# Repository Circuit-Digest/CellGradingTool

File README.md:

# [CellGradingTool](https://circuitdigest.com/videos/diy-modular-cell-grading-machine)

<br>
Testing lithium-ion cells is critical for ensuring their performance, safety, and longevity, particularly in applications such as electric vehicles, energy storage systems, and portable electronics. As these cells can degrade over time, accurate grading tools are necessary to assess their charging, discharging, and overall capacity characteristics. This DIY modular cell grading tool addresses this need by providing a streamlined and scalable solution for testing multiple lithium-ion cells simultaneously while offering precise control over charging and discharging cycles. The tool’s modularity allows users to grade up to 250 cells in parallel, making it a versatile choice for both small and large-scale testing environments. At the heart of the tool is the STM32 G071KBU3 microcontroller, powered by an ADP7118 3.3V LDO regulator. The tool is designed to detect the voltage of each inserted cell and display it on a two-digit seven-segment display, providing instant feedback. When connected to the companion software, users can initiate a test, charging the cell at a constant current of 1A using the TP4056 IC. Upon reaching full charge, the system will disable the charging circuitry and transition into discharge mode, where the discharge current and voltage are monitored through the high-precision INA236 sensor. This setup ensures accurate tracking of both charging and discharging parameters, essential for detailed cell grading.
<br>
Communication between the tool and the PC is managed via the RS485 protocol, utilising the SP485REN transceiver IC. This allows us to connect multiple tools in parallel, with each module being independently controlled by the companion app. The discharge circuit uses an IRF540 MOSFET as a programable DC load and a current control circuit built around the MCP6486 op-amp, ensuring precise current regulation. The DAC output from the STM32G071 is used for adjusting the discharge current, allowing for highly accurate measurements of cell performance under load conditions. The companion software, written in Processing, provides a user-friendly interface for controlling up to 8 modules, with the flexibility to expand to 250 modules. Users can set parameters such as discharge current and voltage limits for each module independently and start tests with a single button click. The software also includes a feature for graphing the discharge voltage curve, providing valuable insights into the cell’s behaviour over time. Even if the cell is removed, the tool retains the test data, ensuring no loss of critical information. With this tool, users can efficiently grade lithium-ion cells and make informed decisions about their suitability for various applications.

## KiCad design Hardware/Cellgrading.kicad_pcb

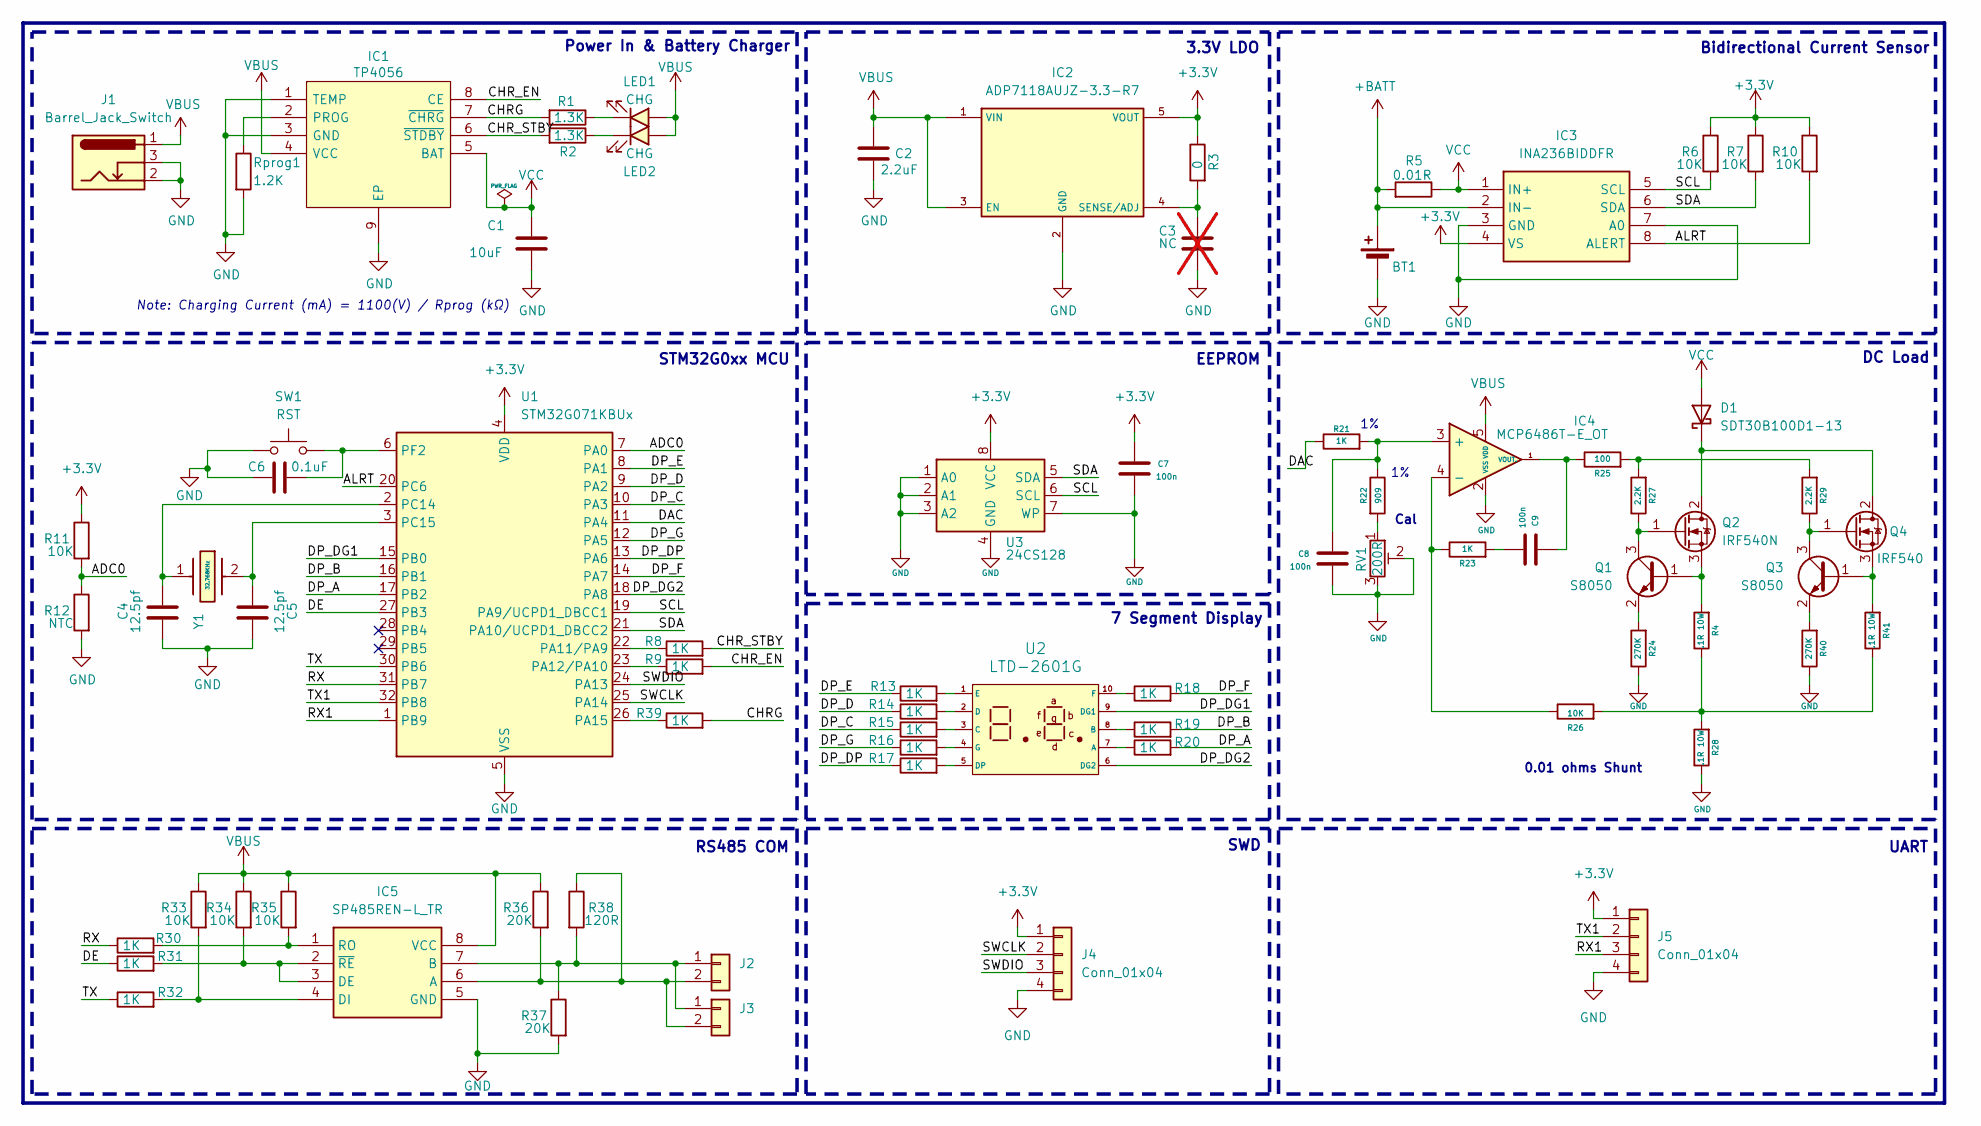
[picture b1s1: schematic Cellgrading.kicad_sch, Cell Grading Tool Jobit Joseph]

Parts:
BT1: Battery_Cell; BAT_1042
C1: 10uF; C_0603_1608Metric
C2: 2.2uF; C_0603_1608Metric
C3: NC; C_0603_1608Metric; not fitted
C4, C5: 12.5pf; C_0603_1608Metric
C6: 0.1uF; C_0603_1608Metric
C7, C8, C9: 100n; C_0603_1608Metric
D1: SDT30B100D1-13; TO252_DIO
IC1: TP4056; SOIC127P600X175-9N; Manufacturer_Part_Number TP4056-42-ESOP8
IC2: ADP7118AUJZ-3.3-R7; SOT95P280X100-5N; Mouser Part Number 584-ADP7118AUJZ3.3R7
IC3: INA236BIDDFR; SOT65P280X110-8N; Mouser Part Number 595-INA236BIDDFR
IC4: MCP6486T-E_OT; SOT95P280X145-5N; Mouser Part Number 494-MCP6486T-E/OT
IC5: SP485REN-L_TR; SOIC127P600X175-8N; Mouser Part Number 701-SP485REN-L/TR
J1: Barrel_Jack_Switch; BarrelJack_Kycon_KLDX-0202-xC_Horizontal
J2, J3: Conn_01x02; JST_PH_S2B-PH-SM4-TB_1x02-1MP_P2.00mm_Horizontal
J4, J5: Conn_01x04; PinHeader_1x04_P2.54mm_Vertical
LED1, LED2: CHG; LED_0603_1608Metric
Q1, Q3: S8050; SOT-23
Q2: IRF540N; TO-220-3_Vertical
Q4: IRF540; TO-220-3_Vertical
R1, R2: 1.3K; R_0603_1608Metric
R3: 0; R_0603_1608Metric
R4, R28, R41: .1R 10W; WSHP2818R0200FEA
R5: 0.01R; WSHP2818R0200FEA
R6, R7, R10, R11, R26, R33, R34, R35: 10K; R_0603_1608Metric
R8, R9, R13, R14, R15, R16, R17, R18, R19, R20, R21, R23, R30, R31, R32, R39: 1K; R_0603_1608Metric
R12: NTC; JST_PH_B2B-PH-K_1x02_P2.00mm_Vertical
R22: 909; R_0603_1608Metric
R24, R40: 270K; R_0603_1608Metric
R25: 100; R_0603_1608Metric
R27, R29: 2.2K; R_0603_1608Metric
R36, R37: 20K; R_0603_1608Metric
R38: 120R; R_0603_1608Metric
RV1: 200R; TRIM_3296W-1-104
Rprog1: 1.2K; R_0603_1608Metric
SW1: RST; Tactile 3x4x2mm TS-A010
U1: STM32G071KBUx; QFN-32-1EP_5x5mm_P0.5mm_EP3.45x3.45mm
U2: LTD-2601G; LTD-2601G_LTO
U3: 24CS128; SOIC-8_3.9x4.9mm_P1.27mm
Y1: 32.768KHz; ECS327734BCTR; Mouser Part Number 520-ECS-.327-7-34BCT

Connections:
+3.3V: C7.1, IC2.5 (VOUT), IC3.4 (VS), J4.1, J5.1, R3.1, R6.1, R7.1, R10.1, R11.1, U1.4 (VDD), U3.8 (VCC)
+BATT: BT1.1 (+), IC3.2 (IN-), R5.2
/ADC0: R11.2, R12.1, U1.7 (PA0)
/ALRT: IC3.8 (ALERT), R10.2, U1.20 (PC6)
/CHRG: IC1.7 (~CHRG), R1.2, R39.2
/CHR_EN: IC1.8 (CE), R9.2
/CHR_STBY: IC1.6 (~STDBY), R2.2, R8.2
/DAC: R21.1, U1.11 (PA4)
/DE: R31.1, U1.27 (PB3)
/DP_A: R20.2, U1.17 (PB2)
/DP_B: R19.2, U1.16 (PB1)
/DP_C: R15.1, U1.10 (PA3)
/DP_D: R14.1, U1.9 (PA2)
/DP_DG1: U1.15 (PB0), U2.9 (DG1)
/DP_DG2: U1.18 (PA8), U2.6 (DG2)
/DP_DP: R17.1, U1.13 (PA6)
/DP_E: R13.1, U1.8 (PA1)
/DP_F: R18.2, U1.14 (PA7)
/DP_G: R16.1, U1.12 (PA5)
/RX: R30.1, U1.31 (PB7)
/RX1: J5.3, U1.1 (PB9)
/SCL: IC3.5 (SCL), R6.2, U1.19 (PA9/UCPD1_DBCC1), U3.6 (SCL)
/SDA: IC3.6 (SDA), R7.2, U1.21 (PA10/UCPD1_DBCC2), U3.5 (SDA)
/SWCLK: J4.2, U1.25 (PA14)
/SWDIO: J4.3, U1.24 (PA13)
/TX: R32.1, U1.30 (PB6)
/TX1: J5.2, U1.32 (PB8)
GND: BT1.2 (-), C1.2, C2.2, C3.2, C4.2, C5.2, C6.1, C7.2, C8.2, IC1.1 (TEMP), IC1.3 (GND), IC1.9 (EP), IC2.2 (GND), IC3.3 (GND), IC3.7 (A0), IC4.2 (VSS), IC5.5 (GND), J1.2, J1.3, J4.4, J5.4, R12.2, R24.1, R28.1, R37.2, R40.1, RV1.2, RV1.3, Rprog1.2, SW1.1, U1.5 (VSS), U1.33 (VSS), U3.1 (A0), U3.2 (A1), U3.3 (A2), U3.4 (GND), U3.7 (WP)
unnamed: C9.2, R23.2
unnamed: D1.2 (K), Q2.2 (D), Q4.2 (D)
unnamed: IC1.2 (PROG), Rprog1.1
unnamed: C3.1, IC2.4 (SENSE/ADJ), R3.2
unnamed: C8.1, IC4.3 (+), R21.2, R22.1
unnamed: IC4.4 (-), R23.1, R26.1
unnamed: C9.1, IC4.1 (VOUT.), R25.1
unnamed: IC5.6 (A), J2.2, J3.2, R36.2, R38.1
unnamed: IC5.7 (B), J2.1, J3.1, R37.1, R38.2
unnamed: IC5.2 (~RE), IC5.3 (DE), R31.2, R34.2
unnamed: IC5.4 (DI), R32.2, R33.2
unnamed: IC5.1 (RO), R30.2, R35.2
unnamed: LED1.1 (K), R1.1
unnamed: LED2.1 (K), R2.1
unnamed: Q1.1 (B), Q2.3 (S), R4.2
unnamed: Q1.3 (C), Q2.1 (G), R27.1
unnamed: Q1.2 (E), R24.2
unnamed: Q3.1 (B), Q4.3 (S), R41.2
unnamed: Q3.3 (C), Q4.1 (G), R29.1
unnamed: Q3.2 (E), R40.2
unnamed: R22.2, RV1.1
unnamed: R25.2, R27.2, R29.2
unnamed: R4.1, R26.2, R28.2, R41.1
unnamed: R8.1, U1.22 (PA11/PA9)
unnamed: R9.1, U1.23 (PA12/PA10)
unnamed: R39.1, U1.26 (PA15)
unnamed: C4.1, U1.2 (PC14), Y1.1
unnamed: C5.1, U1.3 (PC15), Y1.2 (OUT/IN)
unnamed: C6.2, SW1.2, U1.6 (PF2)
unnamed: R20.1, U2.7 (A)
unnamed: R19.1, U2.8 (B)
unnamed: R15.2, U2.3 (C)
unnamed: R14.2, U2.2 (D)
unnamed: R17.2, U2.5 (DP)
unnamed: R13.2, U2.1 (E)
unnamed: R18.1, U2.10 (F)
unnamed: R16.2, U2.4 (G)
VBUS: C2.1, IC1.4 (VCC), IC2.1 (VIN), IC2.3 (EN), IC4.5 (VDD), IC5.8 (VCC), J1.1, LED1.2 (A), LED2.2 (A), R33.1, R34.1, R35.1, R36.1
VCC: C1.1, D1.1 (A), IC1.5 (BAT), IC3.1 (IN+), R5.1

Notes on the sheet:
EEPROM
7 Segment Display
UART
STM32G0xx MCU
3.3V LDO
Power In & Battery Charger
Cal
SWD
Bidirectional Current Sensor
DC Load
0.01 ohms Shunt
Note: Charging Current (mA) = 1100(V) / Rprog (kΩ)
RS485 COM

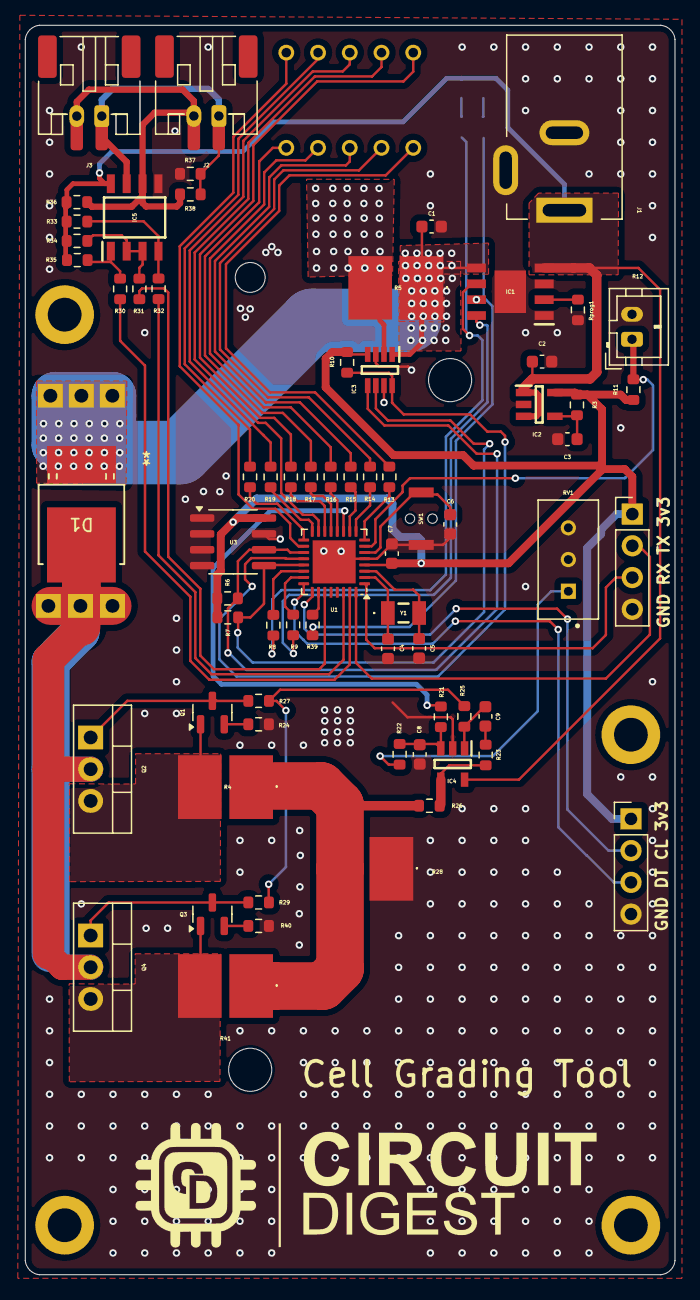
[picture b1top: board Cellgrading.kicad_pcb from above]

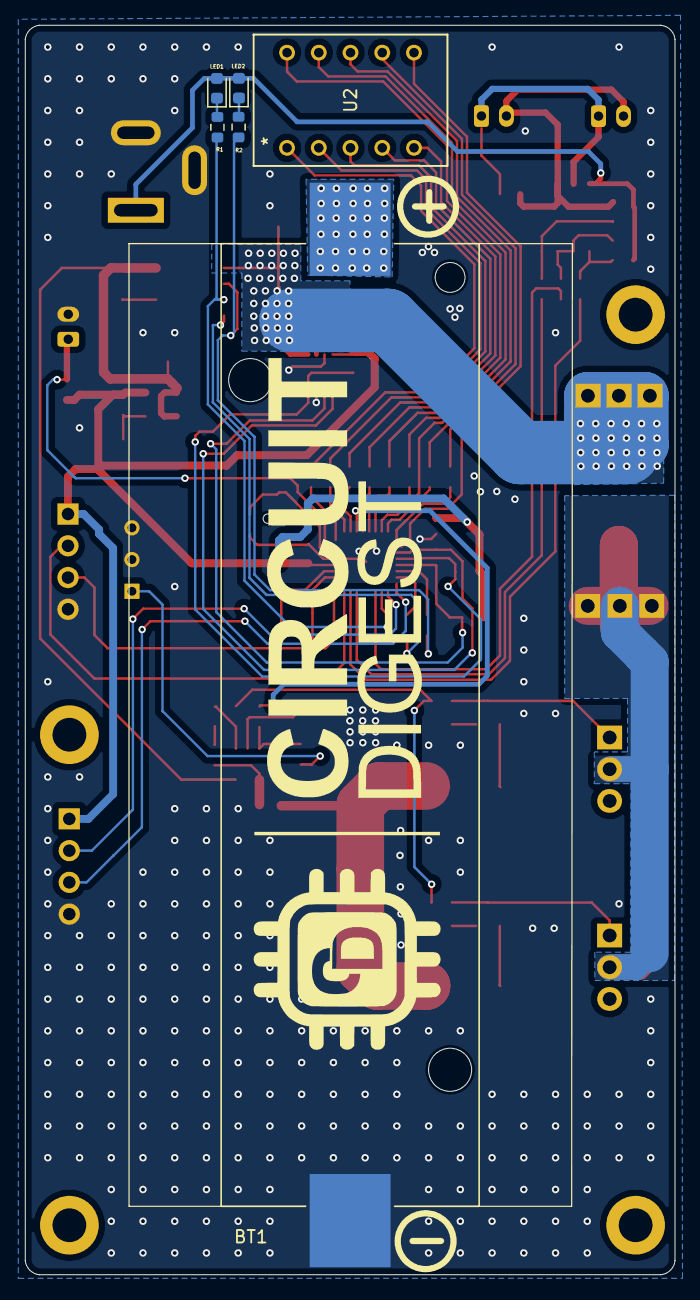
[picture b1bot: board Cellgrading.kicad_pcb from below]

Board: 2 copper layers, 52.0 x 100.0 mm, 75 parts (6 on the bottom side), 67 nets.

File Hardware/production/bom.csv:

Designator,Footprint,Quantity,Value,LCSC Part #
"_6, _5, _4, _3, _2, ",,6,,
BT1,BAT_1042,1,Battery_Cell,
C1,0603,1,10uF,
C2,0603,1,2.2uF,
C3,0603,1,NC,
"C4, C5",0603,2,12.5pf,
C6,0603,1,0.1uF,
"C7, C8, C9",0603,3,100n,
D1,TO252_DIO,1,SDT30B100D1-13,
IC1,SOIC127P600X175-9N,1,TP4056,
IC2,SOT95P280X100-5N,1,ADP7118AUJZ-3.3-R7,
IC3,SOT65P280X110-8N,1,INA236BIDDFR,
IC4,SOT95P280X145-5N,1,MCP6486T-E_OT,
IC5,SOIC127P600X175-8N,1,SP485REN-L_TR,
J1,BarrelJack_Kycon_KLDX-0202-xC_Horizontal,1,Barrel_Jack_Switch,
"J2, J3",JST_PH_S2B-PH-SM4-TB_1x02-1MP_P2.00mm_Horizontal,2,Conn_01x02,
"J4, J5",PinHeader_1x04_P2.54mm_Vertical,2,Conn_01x04,
"LED1, LED2",0603,2,CHG,
"Q1, Q3",SOT-23,2,S8050,
"Q2, Q4",TO-220-3_Vertical,2,IRF540N,
"R1, R2",0603,2,1.3K,
"R10, R11, R26, R33, R34, R35, R6, R7",0603,8,10K,
R12,JST_PH_B2B-PH-K_1x02_P2.00mm_Vertical,1,NTC,
"R13, R14, R15, R16, R17, R18, R19, R20, R23, R30, R31, R32, R39, R8, R9",0603,15,1K,
R21,0603,1,1K,
R22,0603,1,909,
"R24, R40",0603,2,270K,
R25,0603,1,100,
"R27, R29",0603,2,2.2K,
"R28, R4, R41",WSHP2818R0200FEA,3,.01 5W,
R3,0603,1,0,
"R36, R37",0603,2,20K,
R38,0603,1,120R,
R5,WSHP2818R0200FEA,1,0.01R,
RV1,TRIM_3296W-1-104,1,200R,
Rprog1,0603,1,1.2K,
SW1,Tactile 3x4x2mm TS-A010,1,RST,
U1,QFN-32-1EP_5x5mm_P0.5mm_EP3.45x3.45mm,1,STM32G071KBUx,
U2,LTD-2601G_LTO,1,LTD-2601G,
U3,SOIC-8_3.9x4.9mm_P1.27mm,1,24CS32,
Y1,ECS327734BCTR,1,32.768KHz,

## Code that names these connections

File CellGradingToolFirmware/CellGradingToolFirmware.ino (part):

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#define EEPROM_ADDRESS 0x50
// Define variables for RS485
// --------------------
#define DE_PIN PB3  // RS485 transceiver DE pin
#define RE_PIN PB4  // RS485 transceiver RE pin
#define PIN_SERIAL1_TX PB6
#define PIN_SERIAL1_RX PB7
#define SERIAL_BAUDRATE 1000000
const int bufferSize = 200;    // Define buffer size
char inputBuffer[bufferSize];  // Buffer to store incoming data

int numDigits = 2;
int digitPins[2] = { PA8, PB0 };
int segPins[8] = { PB2, PB1, PA3, PA2, PA1, PA7, PA5, PA6 };  // A-G and DP
bool isComCathode = false;
// Define timing variables
unsigned long lastBlinkTime = 0;
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    VFD_HS.write(CID);
    VFD_HS.write(0XD3);
    if (Mode == 0x02) {
      digitalWrite(PA12, LOW);
      Mode = 0X01;
      write8BitToEEPROM(Mode_address, Mode);
      SetCurrent(DCCurrent);
    }
  } else if (command == 0xD7) {
    // Handle command 0xD7
    digitalWrite(PA12, LOW);
    digitalWrite(PA4, LOW);
    pinMode(PA4, INPUT);
    write8BitToEEPROM(Mode_address, 0x09);
    write8BitToEEPROM(DCVoltage_address, 0x00);
    write16BitToEEPROM(DCCurrent_address, 0x0000);
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    // Handle command 0x11
    Mode = 0x09;
    write8BitToEEPROM(Mode_address, Mode);
    digitalWrite(PA12, LOW);
    digitalWrite(PA4, LOW);
    pinMode(PA4, INPUT);
  } else if (command == 0xD5 && ErrC == false) {
    // Handle command 0xD5 (5-byte request)
    startMillis = millis();  // Reset the start time
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    }
    Mode = 0x02;
    write8BitToEEPROM(Mode_address, Mode);
    digitalWrite(PA4, LOW);
    pinMode(PA4, INPUT);
    digitalWrite(PA12, HIGH);
    LastData = 0;
    CUTCapacity = 0;
    LastDC = millis();
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  if (value <= 0) {
    ErrC = true;
    ERC = 0xE0;
    digitalWrite(PA12, LOW);
    digitalWrite(PA4, LOW);
    pinMode(PA4, INPUT);
    Mode = 0x09;
    if (read8BitFromEEPROM(Mode_address) != 0x09) {
      write8BitToEEPROM(Mode_address, Mode);
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  dacValue *= 2;
  // Calculate the DAC value for internal 1.2V Vref
  //uint16_t dacValue = (voltage_DAC / 1.2) * 65535;
  // Output the calculated DAC value to PA4

  //VFD_HS.println("SetC ");

  pinMode(PA4, OUTPUT);
  analogWrite(PA4, dacValue);
}


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      baselineDacValue = 0;
    }

    // Output the adjusted DAC value to PA4
    analogWrite(PA4, baselineDacValue);
  }
}

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void setup() {
  VFD_HS.setPins(DE_PIN, RE_PIN);
  VFD_HS.begin(1000000, SERIAL_8N1);
  pinMode(PA4, INPUT);
  pinMode(PA12, OUTPUT);
  digitalWrite(PA12, LOW);
  //enableInternalVref();
  analogWriteResolution(16);
  pinMode(PA11, INPUT_PULLUP);
  pinMode(PA15, INPUT_PULLUP);

  TIM_TypeDef *Instance = TIM2;  // Using TIM2 for this example
  MyTim = new HardwareTimer(Instance);
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  if (Mode == 0x01) {
    SetCurrent(DCCurrent);
  } else if (Mode == 0x02) {
    digitalWrite(PA12, HIGH);
    LastDC = millis();
  }
  LastUpdate = millis();
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    handleSerialRequest();
  }
  if (Mode == 0X02 && millis() - LastDC > 2000) {
    if (!digitalRead(PA11)) {
      digitalWrite(PA12, LOW);
      StartDC = true;
      LastDCStart = millis();
    }
  } else if (Mode == 0x01) {
    digitalWrite(PA12, LOW);
    SetCurrentFix(DCCurrent);
    if ((millis() - LastCapUpdate) >= 1000) {
      Capacity += (Current * (millis() - LastCapUpdate)) / 3600000.0;
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      DCVoltage = 0;
      DCVoltage2 = 0;
      DCCurrent = 0;
      digitalWrite(PA4, LOW);
      pinMode(PA4, INPUT);
    }
  }
  if (StartDC == true && (millis() - LastDCStart) > 2000) {
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    SetCurrent(DCCurrent);
  }
  if (Mode == 0x09 || Mode == 0x03) {
    digitalWrite(PA12, LOW);
    //digitalWrite(PA4, 0);
  }
}

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

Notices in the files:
CellGradingToolFirmware/CellGradingToolFirmware.ino:
Copyright © Jobit Joseph
Copyright © Semicon Media Pvt Ltd
Copyright © Circuitdigest.com
This code is licensed under the following conditions:
1. Non-Commercial Use:
This program is free software: you can redistribute it and/or modify it
